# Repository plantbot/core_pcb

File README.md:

# Open Plantbot

Because growing plants is hard work and nobody ain't got no time for that anymore. This project was started after I managed to kill a plant my mother got me for my birthday last year because it was "unkillable". Ha.

This project aims to build an open source tool that provides environmental sensors for regular house plants as well as hydroponic systems.

Monitoring can either be done locally or via a "cloud" or not at all with add-on ports for pumps and future expansions (or your own?).

The goal is to eventually provide a block-based programming interface so that even people who don't enjoy writing C code (tzzz...who doesn't? :P) can customise their plantbot to do what they want.

### Current specs

Here is a list of current specs with notes about how they integrate/ work

1x Wifi enabled microprocessor

 - Can be programmed via RX/TX serial lines
 - USB/ OTA programming will be added later

4x Analog sensor mounts (for temperature, soil moisture, light, ...)

 - Variable gain amplifier can be used on a per-channel basis
 - Signal offset results in optimal reading per sensor type
 
2x I²C expansion ports for additional sensors or expansions

16-pin shield header for user (or future) expansion boards

Low-power sleep mode for the entire board/ expansion circuitry

### Current state

The board was re-designed recently in Rev A2. Prototypes were ordered and partially assembled. Further testing on the board layout and circuit design needs to be performed.

The firmware is largely unwritten.

Following are some pictures. Enjoy :)

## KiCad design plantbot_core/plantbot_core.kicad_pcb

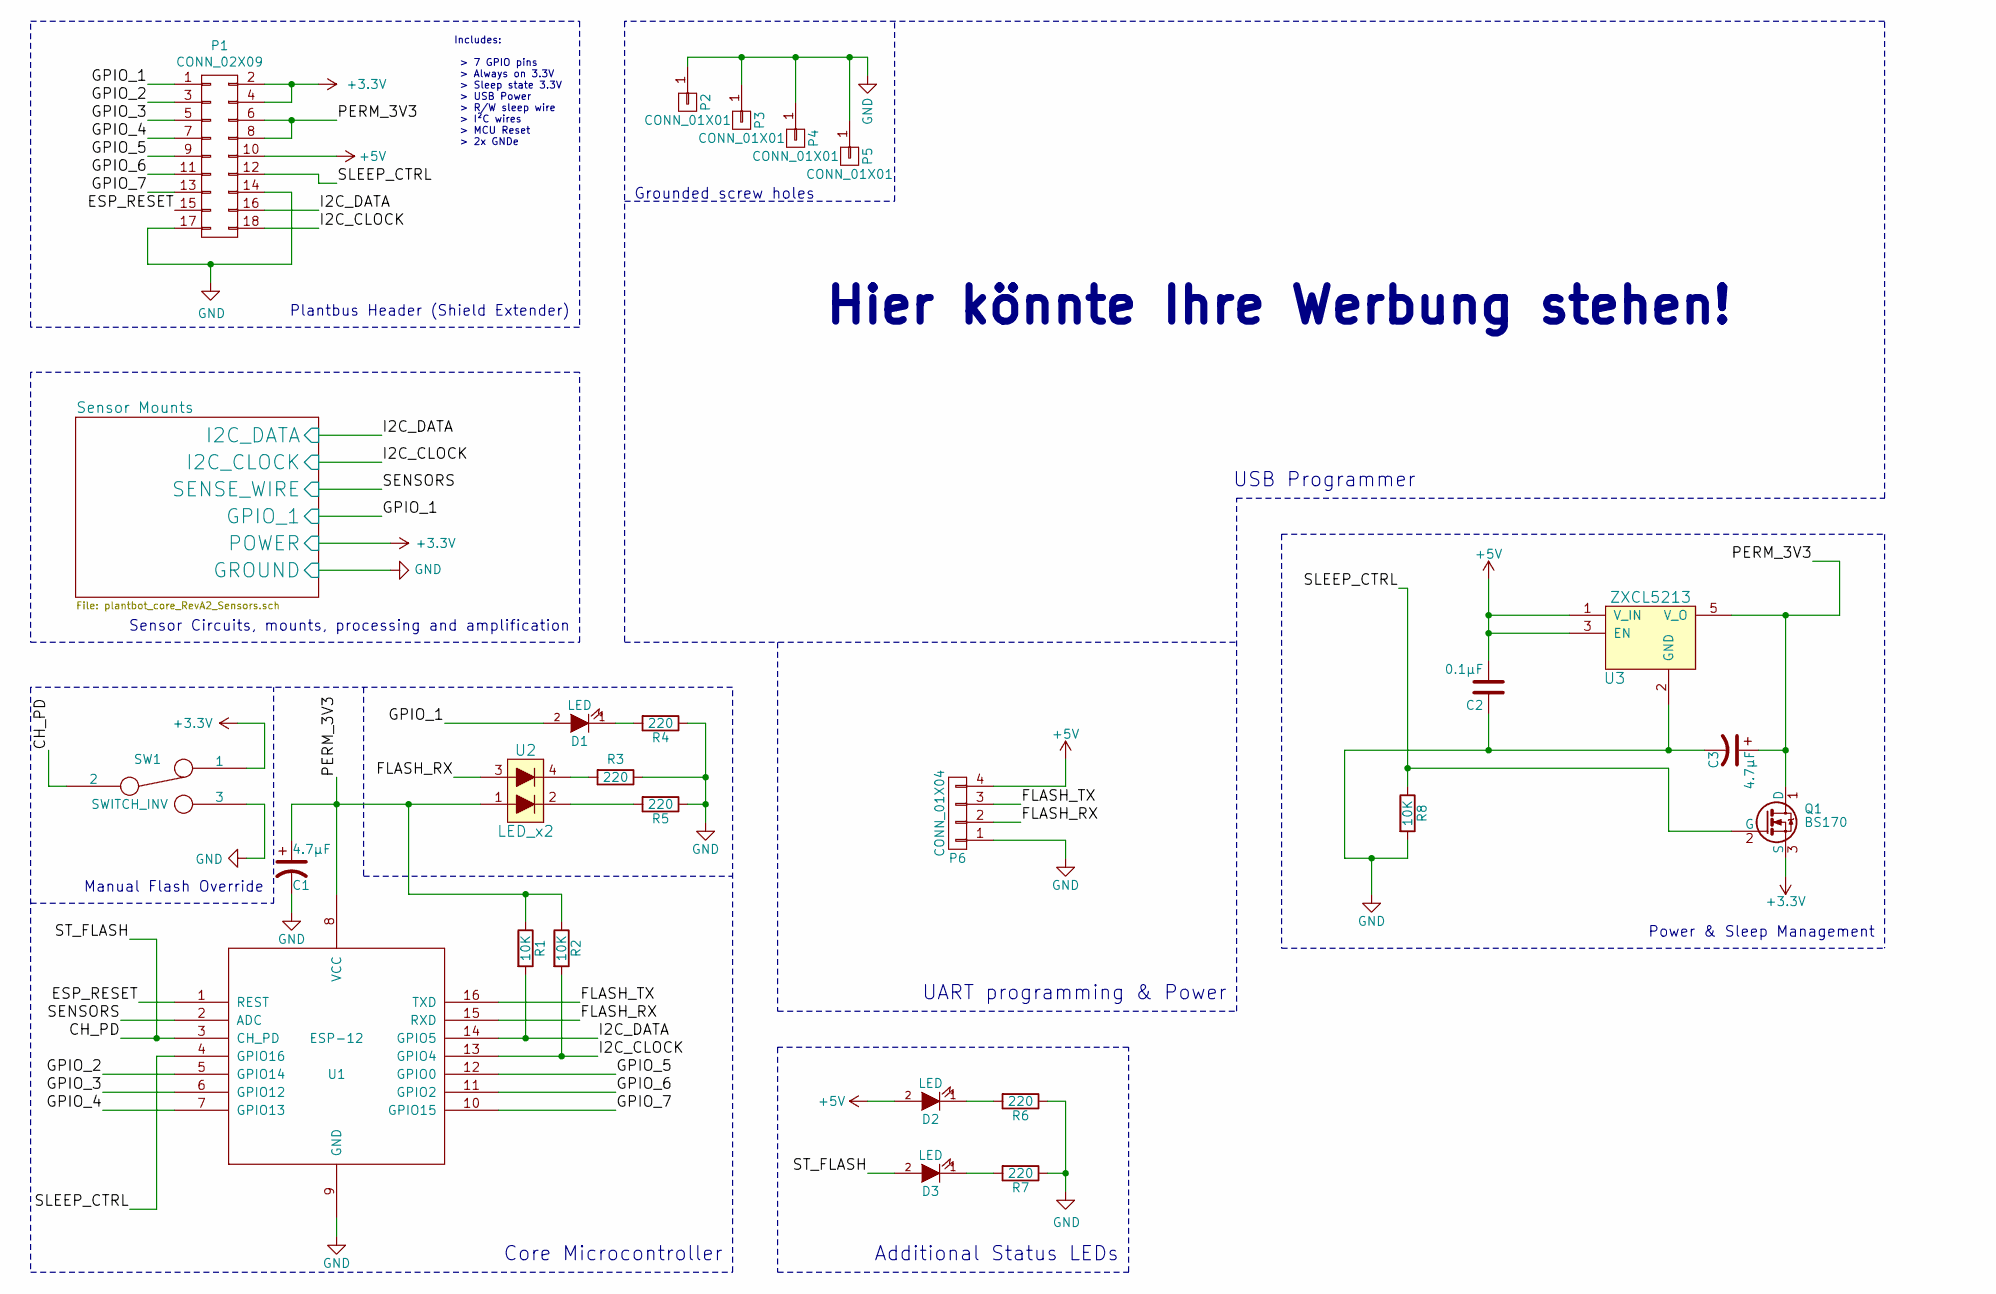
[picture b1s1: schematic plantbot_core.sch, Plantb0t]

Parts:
C1, C3: 4.7µF; c_elec_4x4.5
C2: 0.1µF; C_0805
D1, D2, D3: LED; knightbright_3216
P1: CONN_02X09; Socket_Strip_Straight_2x09
P2, P3, P4, P5: CONN_01X01; 1pin
P6: CONN_01X04; Socket_Strip_Straight_1x04
Q1: BS170; SOT-23_Handsoldering
R1, R2, R8: 10K; R_0603
R3, R4, R5, R6, R7: 220; R_0603
SW1: SWITCH_INV; SSAJ120100
U1: ESP-12
U2: LED_x2; SML-521
U3: ZXCL5213; SOT-23-5

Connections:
+3V3: P1.2, P1.4, Q1.3 (S), SW1.1; also elsewhere on the board
+5V: C2.2, D2.2 (A), P1.10, P6.4, U3.1 (V_IN), U3.3 (EN)
/CH_PD: D3.2 (A), SW1.2, U1.3 (CH_PD)
/ESP_RESET: P1.15, U1.1 (REST)
/FLASH_RX: P6.2, U1.15 (RXD), U2.3
/FLASH_TX: P6.3, U1.16 (TXD)
/GPIO_1: D1.2 (A), P1.1; also elsewhere on the board
/GPIO_2: P1.3, U1.5 (GPIO14)
/GPIO_3: P1.5, U1.6 (GPIO12)
/GPIO_4: P1.7, U1.7 (GPIO13)
/GPIO_5: P1.9, U1.12 (GPIO0)
/GPIO_6: P1.11, U1.11 (GPIO2)
/GPIO_7: P1.13, U1.10 (GPIO15)
/I2C_CLOCK: P1.18, R2.2, U1.13 (GPIO4); also elsewhere on the board
/I2C_DATA: P1.16, R1.2, U1.14 (GPIO5); also elsewhere on the board
/PERM_3V3: C1.1, C3.1, P1.6, P1.8, Q1.1 (D), R1.1, R2.1, U1.8 (VCC), U2.1, U3.5 (V_O)
/SENSORS: U1.2 (ADC); also elsewhere on the board
/SLEEP_CTRL: P1.12, Q1.2 (G), R8.1, U1.4 (GPIO16)
GND: C1.2, C2.1, C3.2, P1.14, P1.17, P2.1, P3.1, P4.1, P5.1, P6.1, R3.1, R4.1, R5.1, R6.1, R7.1, R8.2, SW1.3, U1.9 (GND), U3.2 (GND); also elsewhere on the board
unnamed: D1.1 (K), R4.2
unnamed: D2.1 (K), R6.2
unnamed: D3.1 (K), R7.2
unnamed: R3.2, U2.4
unnamed: R5.2, U2.2

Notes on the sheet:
Sensor Circuits, mounts, processing and amplification
Power & Sleep Management
Plantbus Header (Shield Extender)
UART programming & Power
USB Programmer
Manual Flash Override
Core Microcontroller
Additional Status LEDs
Includes: > 7 GPIO pins > Always on 3.3V > Sleep state 3.3V > USB Power > R/W sleep wire > I²C wires > MCU Reset > 2x GNDe
Grounded screw holes
Hier könnte Ihre Werbung stehen!

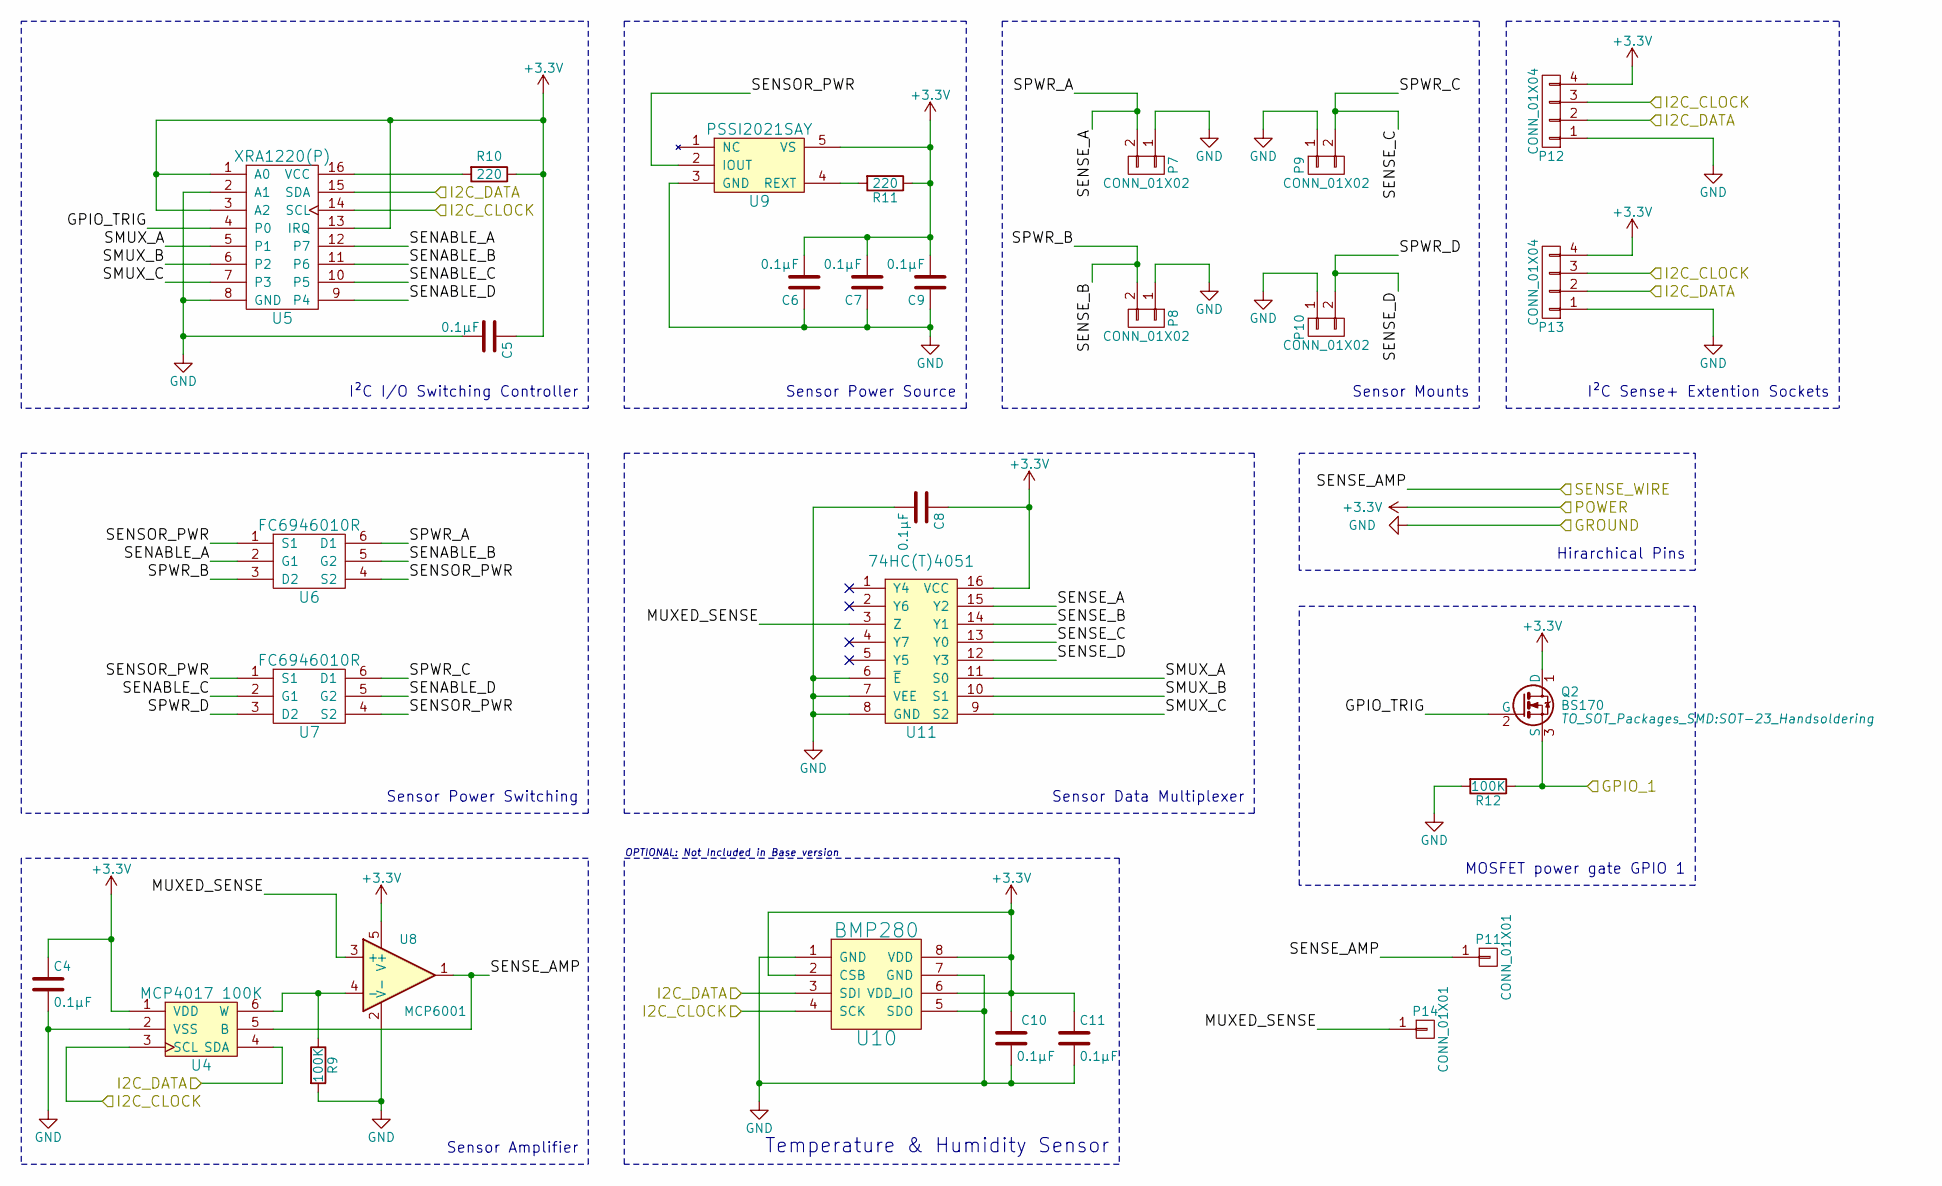
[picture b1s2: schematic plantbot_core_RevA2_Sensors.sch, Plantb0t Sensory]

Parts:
C4, C5, C6, C7, C8, C9, C10, C11: 0.1µF; C_0805
P7, P8, P9, P10: CONN_01X02; Socket_Strip_Straight_1x02
P11, P14: CONN_01X01; 1pin-SMD
P12, P13: CONN_01X04; Socket_Strip_Straight_1x04
Q2: BS170; SOT-23_Handsoldering
R9, R12: 100K; R_0603
R10, R11: 220; R_0603
U4: MCP4017 100K; SC-70-6_Handsoldering
U5: XRA1220(P); TSSOP-16_4.4x5mm_Pitch0.65mm
U6, U7: FC6946010R; sot666
U8: MCP6001; SOT-23-5
U9: PSSI2021SAY; SOT-353
U10: BMP280; BME280
U11: 74HC(T)4051; TSSOP-16_4.4x5mm_Pitch0.65mm

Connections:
+3V3: C4.1, C5.1, C6.2, C7.2, C8.1, C9.2, C10.1, C11.1, P12.4, P13.4, Q2.1 (D), R10.1, R11.1, U4.1 (VDD), U5.1 (A0), U5.3 (A2), U5.13 (IRQ), U8.5 (V+), U9.5 (VS), U10.2 (CSB), U10.6 (VDD_IO), U10.8 (VDD), U11.16 (VCC); also elsewhere on the board
/GPIO_1: Q2.3 (S), R12.1; also elsewhere on the board
/I2C_CLOCK: P12.3, P13.3, U4.3 (SCL), U5.14 (SCL), U10.4 (SCK); also elsewhere on the board
/I2C_DATA: P12.2, P13.2, U4.4 (SDA), U5.15 (SDA), U10.3 (SDI); also elsewhere on the board
/SENSORS: P11.1, U4.5 (B), U8.1; also elsewhere on the board
/Sensor Mounts/GPIO_TRIG: Q2.2 (G), U5.4 (P0)
/Sensor Mounts/MUXED_SENSE: P14.1, U8.3 (+), U11.3 (Z)
/Sensor Mounts/SENABLE_A: U5.12 (P7), U6.2 (G1)
/Sensor Mounts/SENABLE_B: U5.11 (P6), U6.5 (G2)
/Sensor Mounts/SENABLE_C: U5.10 (P5), U7.2 (G1)
/Sensor Mounts/SENABLE_D: U5.9 (P4), U7.5 (G2)
/Sensor Mounts/SENSE_A: P7.2, U6.6 (D1), U11.15 (Y2)
/Sensor Mounts/SENSE_B: P8.2, U6.3 (D2), U11.14 (Y1)
/Sensor Mounts/SENSE_C: P9.2, U7.6 (D1), U11.13 (Y0)
/Sensor Mounts/SENSE_D: P10.2, U7.3 (D2), U11.12 (Y3)
/Sensor Mounts/SENSOR_PWR: U6.1 (S1), U6.4 (S2), U7.1 (S1), U7.4 (S2), U9.2 (IOUT)
/Sensor Mounts/SMUX_A: U5.5 (P1), U11.11 (S0)
/Sensor Mounts/SMUX_B: U5.6 (P2), U11.10 (S1)
/Sensor Mounts/SMUX_C: U5.7 (P3), U11.9 (S2)
GND: C4.2, C5.2, C6.1, C7.1, C8.2, C9.1, C10.2, C11.2, P7.1, P8.1, P9.1, P10.1, P12.1, P13.1, R9.2, R12.2, U4.2 (VSS), U5.2 (A1), U5.8 (GND), U8.2 (V-), U9.3 (GND), U10.1 (GND), U10.5 (SDO), U10.7 (GND), U11.6 (~E), U11.7 (VEE), U11.8 (GND); also elsewhere on the board
unnamed: R9.1, U4.6 (W), U8.4 (-)
unnamed: R10.2, U5.16 (VCC)
unnamed: R11.2, U9.4 (REXT)

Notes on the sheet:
I²C I/O Switching Controller
Sensor Power Switching
Sensor Power Source
Sensor Data Multiplexer
Sensor Mounts
Sensor Amplifier
Hirarchical Pins
I²C Sense+ Extention Sockets
Temperature & Humidity Sensor
OPTIONAL: Not Included in Base version
MOSFET power gate GPIO 1

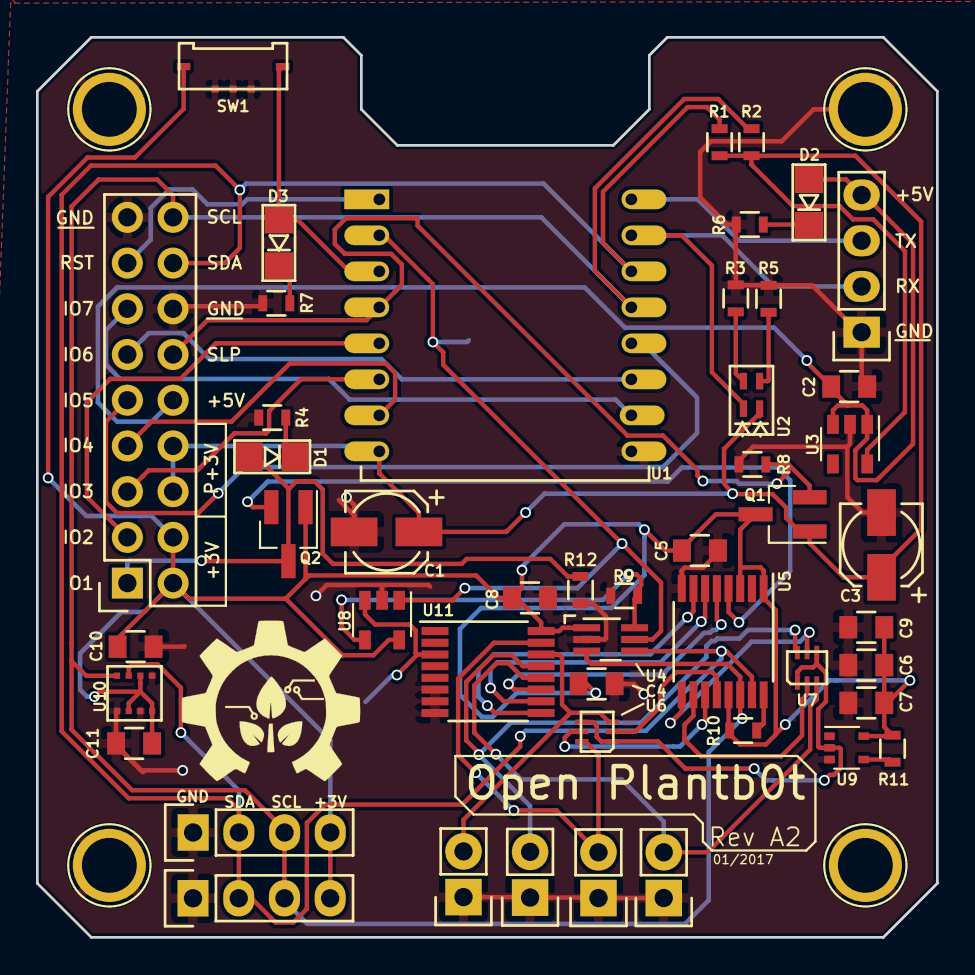
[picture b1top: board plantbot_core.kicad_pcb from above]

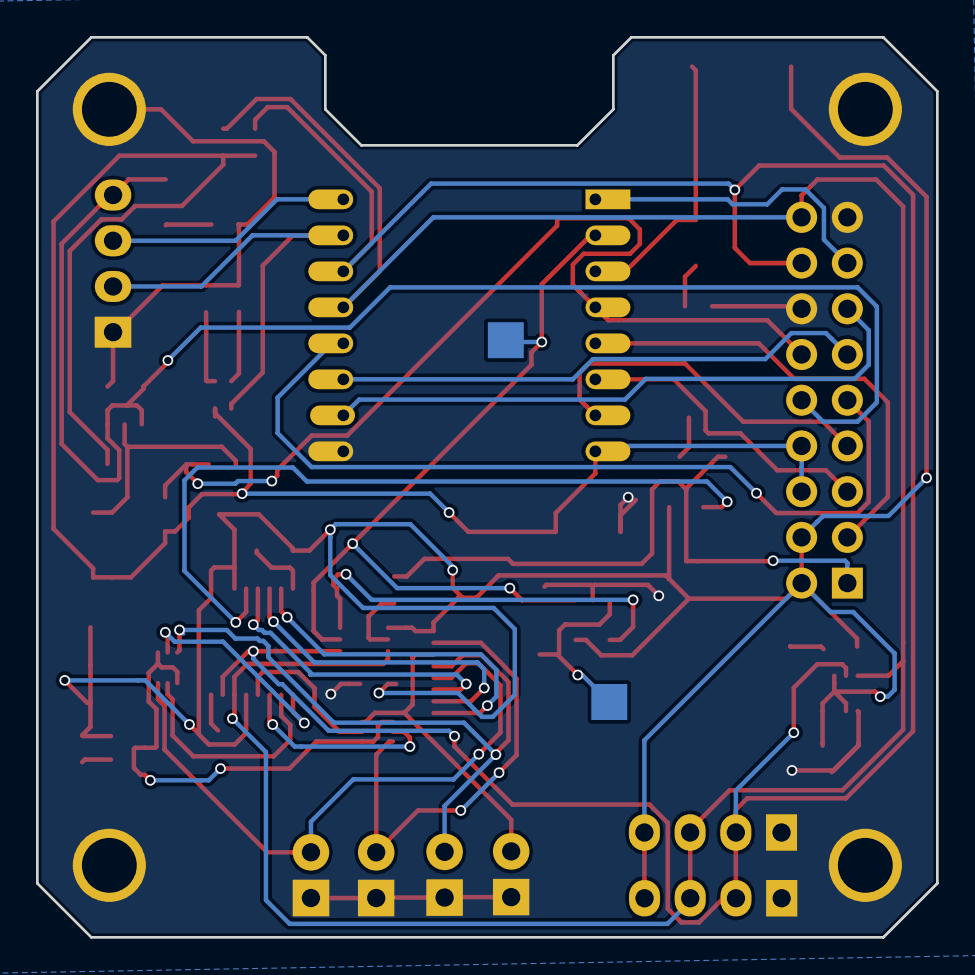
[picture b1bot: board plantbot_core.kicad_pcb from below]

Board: 2 copper layers, 50.0 x 50.0 mm, 54 parts (2 on the bottom side), 41 nets.

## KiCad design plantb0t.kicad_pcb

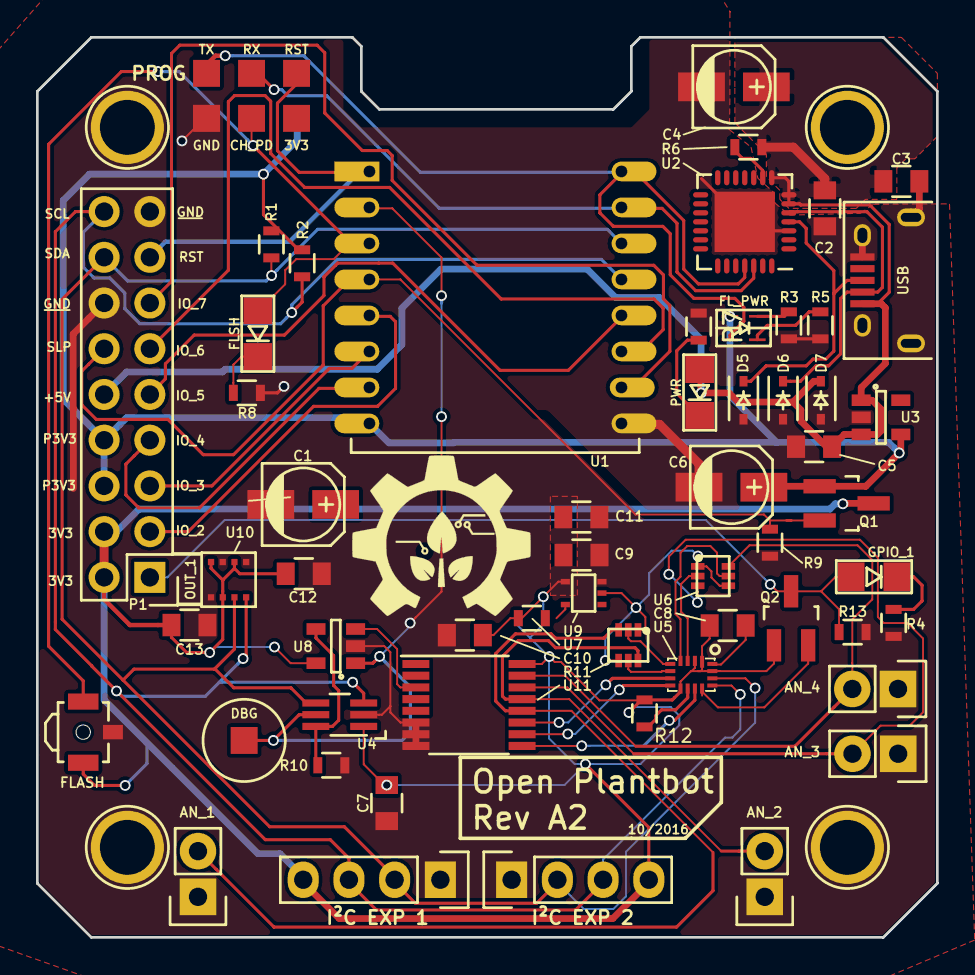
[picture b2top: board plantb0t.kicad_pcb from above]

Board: 2 copper layers, 50.0 x 50.0 mm, 61 parts (0 on the bottom side), 45 nets.

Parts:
AN_1, AN_2, AN_3, AN_4: CONN_01X02; Pin_Header_Straight_1x02
C1, C4, C6: 4.7µF; c_elec_4x5.3
C2: 1µF; C_0805
C3, C5, C7, C8, C9, C10, C11, C12, C13: 0.1µF; C_0805
D5, D6, D7: Zener; SOD-323
DBG: CONN_01X01; 1pin
FLASH: SWITCH_INV; SW_SPST_B3U-3100P-B
FLSH: LED; knightbright_3216
FL_PWR: LEDx2; SML-52
GPIO_1: LED; knightbright_3216
I²C EXP 1, I²C EXP 2: CONN_01X04; Pin_Header_Straight_1x04
P1: CONN_02X09; Pin_Header_Straight_2x09
P10, P11, P12, P13: CONN_01X01; 1pin
PROG: CONN_02X03; prog_6pin
PWR: LED; knightbright_3216
Q1, Q2: BS170; SOT-23_Handsoldering
R1, R2, R9, R12: 10K; R_0603
R3, R4, R5, R7, R8: 220; R_0603
R6: 4.7k; R_0603
R10, R13: 100K; R_0603
R11: R; R_0603
U1: ESP-12
U2: CP2102; QFN-28-1EP_5x5mm_Pitch0.5mm
U3: ZXCL5213V30H5CT-ND; SOT-23-5
U4: MCP4017 100K; SC-70-6_Handsoldering
U5: FXL6408; UMLP16
U6, U7: FC6946010R; sot666
U8: MCP6001; SOT-23-5
U9: PSSI2021SAY; SOT-353
U10: BMP280; BME280
U11: 74HC(T)4051; TSSOP-16_4.4x5mm_Pitch0.65mm
USB: USB_OTG; USB_Micro-B

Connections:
+3V3: C7.1, C8.1, C9.2, C10.1, C11.2, C12.1, C13.1, FLASH.1, I²C EXP 1.4, I²C EXP 2.4, P1.2, P1.4, Q1.3, Q2.1, R11.1, R12.1, U4.1, U5.1, U5.2, U5.9, U5.15, U8.5, U9.4, U10.2, U10.6, U10.8, U11.16
+5V: C2.1, C3.2, C4.1, C5.2, D7.1, P1.10, PWR.2, R6.2, U2.6, U2.7, U2.8, U3.1, U3.3, USB.1
/CH_PD: FLASH.2, FLSH.2, PROG.3, U1.3
/ESP_RESET: P1.15, PROG.6, U1.1
/FLASH_RX: PROG.4, U1.15, U2.26
/FLASH_TX: FL_PWR.1, PROG.2, U1.16, U2.25
/GPIO_1: GPIO_1.2, P1.1, Q2.3, R13.1
/GPIO_2: P1.3, U1.5
/GPIO_3: P1.5, U1.6
/GPIO_4: P1.7, U1.7
/GPIO_5: P1.9, U1.12
/GPIO_6: P1.11, U1.11
/GPIO_7: P1.13, U1.10
/I2C_CLOCK: I²C EXP 1.3, I²C EXP 2.3, P1.18, R2.2, U1.13, U4.3, U5.13, U10.4
/I2C_DATA: I²C EXP 1.2, I²C EXP 2.2, P1.16, R1.2, U1.14, U4.4, U5.14, U10.3
/PERM_3V3: C1.1, C6.1, FL_PWR.2, P1.6, P1.8, PROG.5, Q1.1, R1.1, R2.1, U1.8, U3.4
/SENSORS: DBG.1, U1.2, U4.5, U8.1
/SLEEP_CTRL: P1.12, Q1.2, R9.1, U1.4
/Sensor Mounts/GPIO_TRIG: Q2.2, U5.12
/Sensor Mounts/MUXED_SENSE: U8.3, U11.3
/Sensor Mounts/SENABLE_A: U5.3, U6.2
/Sensor Mounts/SENABLE_B: U5.4, U6.5
/Sensor Mounts/SENABLE_C: U5.5, U7.2
/Sensor Mounts/SENABLE_D: U5.6, U7.5
/Sensor Mounts/SENSE_A: AN_4.2, U6.6, U11.15
/Sensor Mounts/SENSE_B: AN_3.2, U6.3, U11.14
/Sensor Mounts/SENSE_C: AN_2.2, U7.6, U11.13
/Sensor Mounts/SENSE_D: AN_1.2, U7.3, U11.12
/Sensor Mounts/SENSOR_PWR: U6.1, U6.4, U7.1, U7.4, U9.2
/Sensor Mounts/SMUX_A: U5.7, U11.11
/Sensor Mounts/SMUX_B: U5.8, U11.10
/Sensor Mounts/SMUX_C: U5.11, U11.9
/USB_D+: D5.1, U2.4, USB.3
/USB_D-: D6.1, U2.5, USB.2
GND: AN_1.1, AN_2.1, AN_3.1, AN_4.1, C1.2, C2.2, C3.1, C4.2, C5.1, C6.2, C7.2, C9.1, C10.2, C11.1, C12.2, C13.2, D5.2, D6.2, D7.2, FLASH.3, I²C EXP 1.1, I²C EXP 2.1, P1.14, P1.17, P10.1, P11.1, P12.1, P13.1, PROG.1, R3.1, R4.1, R5.1, R7.1, R8.1, R9.2, R10.2, R13.2, U1.9, U2.3, U2.29, U3.2, U4.2, U8.2, U9.3, U10.1, U10.5, U10.7, U11.6, U11.7, U11.8, USB.5, USB.6
unnamed: C8.2, U5.16
unnamed: GPIO_1.1, R4.2
unnamed: PWR.1, R7.2
unnamed: FLSH.1, R8.2
unnamed: FL_PWR.3, R3.2
unnamed: FL_PWR.4, R5.2
unnamed: R6.1, U2.9
unnamed: R10.1, U4.6, U8.4
unnamed: R11.2, U9.5
unnamed: R12.2, U5.10

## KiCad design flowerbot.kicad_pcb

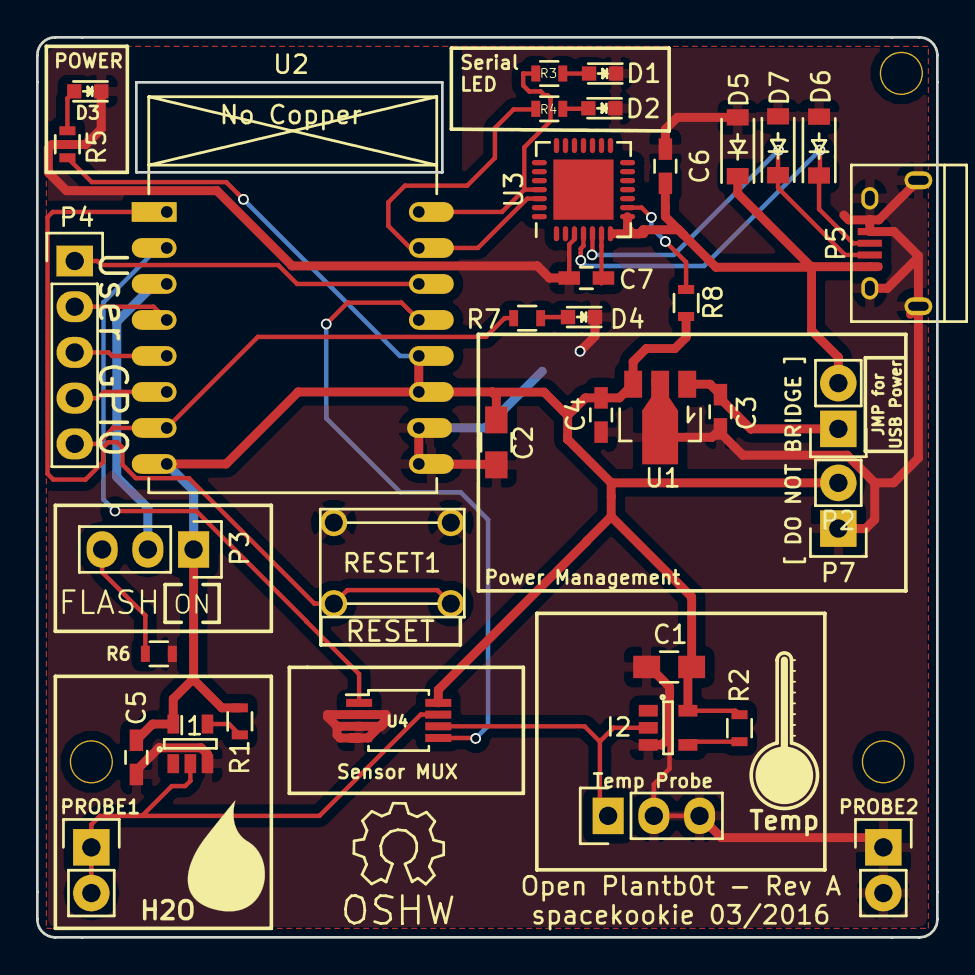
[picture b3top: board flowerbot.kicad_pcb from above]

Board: 2 copper layers, 50.0 x 50.0 mm, 37 parts (0 on the bottom side), 28 nets.

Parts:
C1, C2: 0.1µF; C_0805_HandSoldering
C3, C4: C; C_0603_HandSoldering
C5, C6, C7: 0.1µF; C_0603_HandSoldering
D1, D2, D3, D4: LED; LED-0603
D5, D6, D7: ZENER; SOD-123
I1, I2: NXP_PSSI2021SAY; SOT-23-5
P2: CONN_01X02; Pin_Header_Straight_1x02
P3: CONN_01X03; Pin_Header_Straight_1x03
P4: CONN_01X05; Pin_Header_Straight_1x05
P5: USB_OTG; USB_Micro-B
P7: CONN_01X02; Socket_Strip_Straight_1x02
PROBE1, PROBE2: CONN_01X02; Pin_Header_Straight_1x02
R1, R2: 619; R_0603
R3, R4, R5, R7: 120; R_0603
R6, R8: 4.7k; R_0603
RESET1: SW_BTN; SW_TACTILE_SHALLOW
Temp Probe: CONN_01X03; Socket_Strip_Straight_1x03
U1: LM2937_3.3V; SOT89-3_Housing
U2: ESP-07v2
U3: CP2102; QFN-28-1EP_5x5mm_Pitch0.5mm
U4: 74LVC1G53; MSOP-8_3x3mm_Pitch0.65mm

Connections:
+3V3: C1.1, C2.1, C4.1, C5.2, I1.5, I2.5, P3.1, P7.2, R1.1, R2.1, R5.2, R8.2, U1.3, U2.8, U2.11, U2.12, U4.8
+5V: C6.2, D5.1, P2.2, P5.1, U3.7, U3.8
/AMUX_SELECT: U2.13, U4.5
/CH_PD: P3.2, U2.3
/H2O_PROBE: I1.2, PROBE1.1, PROBE1.2, U4.7
/IO_5: P4.1, U2.14
/IO_12: P4.4, U2.6
/IO_13: P4.5, R7.1, U2.7
/IO_14: P4.3, U2.5
/IO_16: P4.2, U2.4
/PROBE_SEL: U2.2, U4.1
/RES: RESET1.1, U2.1
/RX_D: R4.2, U2.15, U3.26
/TEMP_PROBE: I2.2, Temp Probe.1, U4.6
/TX_D: R3.2, U2.16, U3.25
GND: C1.2, C2.2, C3.1, C4.2, C5.1, C6.1, C7.1, D1.1, D2.1, D3.1, D4.1, D5.2, D6.2, D7.2, I1.3, I2.3, P5.4, P5.5, P5.6, P7.1, PROBE2.1, PROBE2.2, R6.2, RESET1.2, Temp Probe.2, Temp Probe.3, U1.2, U2.9, U2.10, U3.3, U4.2, U4.3, U4.4
unnamed: C3.2, P2.1, U1.1
unnamed: C7.2, U3.6
unnamed: D1.2, R3.1
unnamed: D2.2, R4.1
unnamed: D3.2, R5.1
unnamed: D4.2, R7.2
unnamed: D6.1, P5.3, U3.4
unnamed: D7.1, P5.2, U3.5
unnamed: I1.4, R1.2
unnamed: I2.4, R2.2
unnamed: P3.3, R6.1
unnamed: R8.1, U3.9

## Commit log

2016-03-28 Adding initial project files.
2016-03-28 Adding a nice rendering
2016-03-28 Blaaaa
2016-03-29 Fleshing out Revision A of the PCB.
2016-03-29 Adding more silkscreen and sensor multiplexing.
2016-03-29 Adding lots of gerber files, some new pictures, etc.
2016-05-21 Script to test the moisture curve through the life cicle of a plant pot.
2016-05-22 Adding some files.
2016-05-24 Cleaning up Repository.
2016-06-18 Adding research material and schematics for the Rev A2 board.
2016-09-26 Updating a lot of stuff...
2016-09-27 Updating some firmware ideas
2016-09-29 Loading in new kookie libs
    Updating Bill of Material for capacitors
2016-10-01 Starting Rev A2 board routing
2016-10-17 Starting routing from scratch
2016-10-17 Fiddling with the 5V plane for decoupling around the USB programmer
2016-10-17 Adding a few GPIO pins to the header and wiring up I²C expander sockets
2016-10-18 Moving analog section and adding power gating
2016-10-18 Correcting a wire issue around bosch sensor Finishing basic routing I²C goes through VIAS. Is that an issue?
2016-10-18 Tweaking the ground plane and fixing missing traces
2016-10-18 Finishing up board Revision A 2.0
2016-10-21 Majorly updating the board. Moving some components. Changing the Plantbot logo \o/
2017-01-01 Updating a bunch of project files to the state that went into production on 2017-01-01
2017-03-27 Adding stuff to README
2017-03-29 Moving documentation over to fodt. Adding a bunch of stuff. Merging to master because yolo
2017-08-07 Renaming project stuff
2017-08-07 Changing the library paths to work on my computer. This really isn't ideal...how am I supposed to handle this?
2017-08-07 Adding some logo thingy
2017-09-19 Fixing some KiCad issues (I think)
